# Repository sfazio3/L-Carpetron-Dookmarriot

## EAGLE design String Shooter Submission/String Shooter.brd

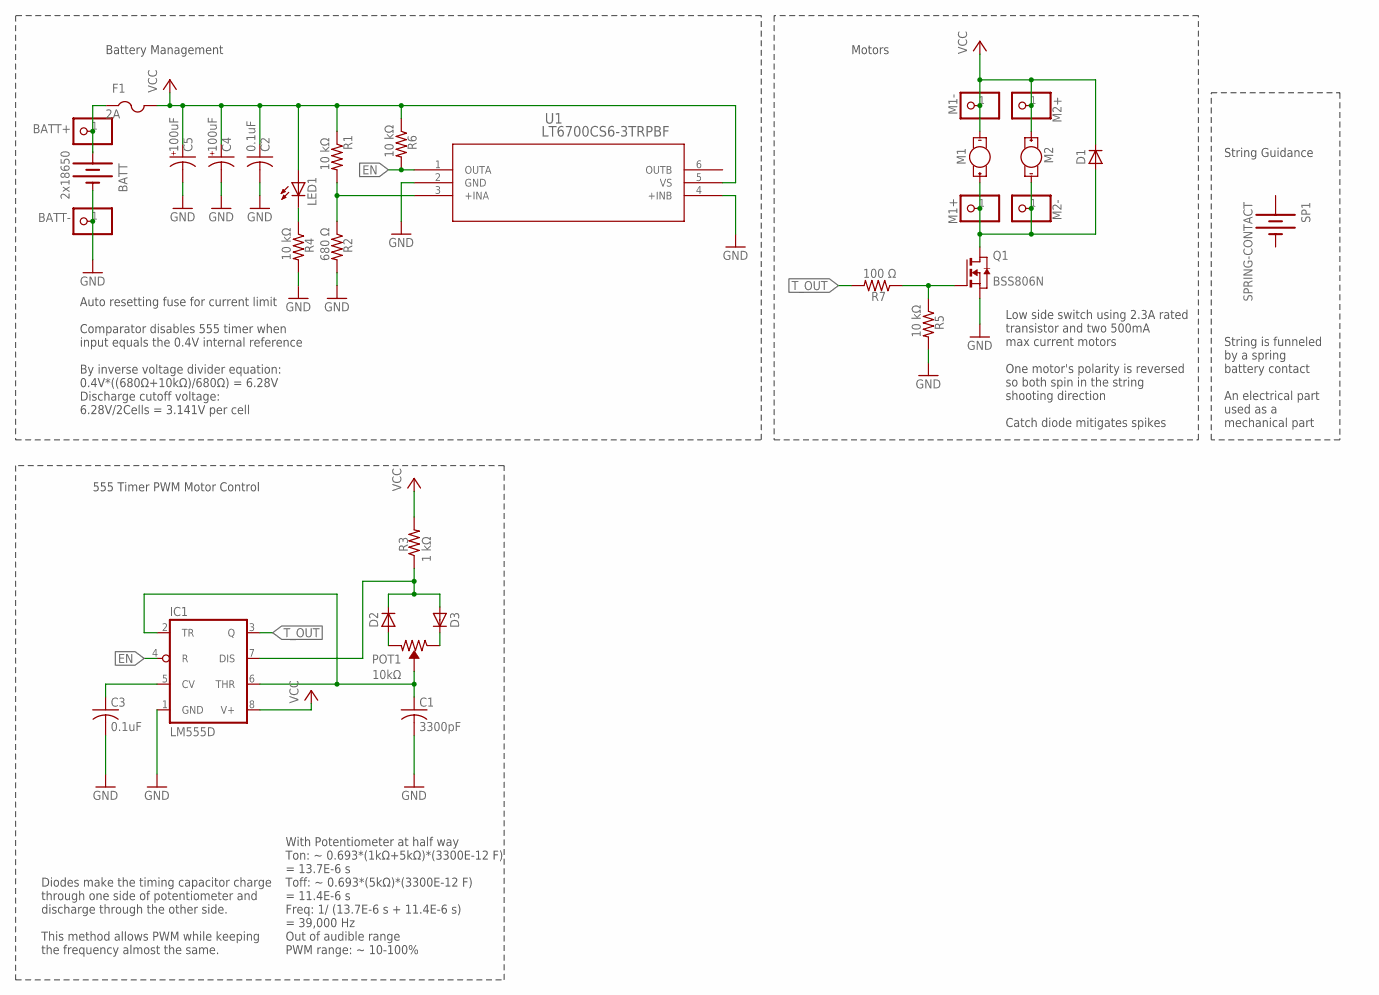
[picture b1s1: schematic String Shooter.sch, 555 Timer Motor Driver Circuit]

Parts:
BATT: 2x18650; BATTERY-CASE
BATT+: PINHD-1X1CB; 1X01-CLEANBIG
BATT-: PINHD-1X1CB; 1X01-CLEANBIG
C1: 3300pF; C0603
C2, C3: 0.1uF; C0603
C4, C5: 100uF; E22-6
D1, D2, D3: DIODE-DO-214AC; DO-214AC
F1: 2A; R1206
IC1: LM555D; SO08
LED1: LEDCHIP-LED0603; CHIP-LED0603
M1, M2: LITTLE-MOTOR; DC_MOTOR
M1+, M1-, M2+, M2-: PINHD-1X1CB; 1X01-CLEANBIG
POT1: 10kΩ; THUMBWHEEL-POT
Q1: BSS806N; SOT-23-3
R1, R4, R5, R6: 10 kΩ; R0603
R2: 680 Ω; R0603
R3: 1 kΩ; R0603
R7: 100 Ω; R0603
SP1: SPRING-CONTACT
U1: LT6700CS6-3TRPBF; TSOT-23_S6

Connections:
EN: IC1.4 (R), R6.2, U1.1 (OUTA)
GND: BATT-.1, C1.2, C2.2, C3.2, C4.-, C5.-, IC1.1 (GND), Q1.2 (S), R2.2, R4.2, R5.2, U1.2 (GND), U1.4 (+INB)
unnamed: D2.A, POT1.P$1 (CCW)
unnamed: D1.A, M1+.1, M2-.1, Q1.3 (D)
unnamed: C3.1, IC1.5 (CV)
unnamed: D3.C, POT1.P$3 (CW)
unnamed: D2.C, D3.A, IC1.7 (DIS), R3.1
unnamed: Q1.1 (G), R5.1, R7.1
unnamed: R1.2, R2.1, U1.3 (+INA)
unnamed: LED1.C, R4.1
unnamed: BATT+.1, F1.1
THR: C1.1, IC1.2 (TR), IC1.6 (THR), POT1.P$2 (WIPER)
T_OUT: IC1.3 (Q), R7.2
VCC: C2.1, C4.+, C5.+, D1.C, F1.2, IC1.8 (V+), LED1.A, M1-.1, M2+.1, R1.1, R3.2, R6.1, U1.5 (VS)

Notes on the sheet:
Diodes make the timing capacitor charge through one side of potentiometer and discharge through the other side. This method allows PWM while keeping the frequency almost the same.
Low side switch using 2.3A rated transistor and two 500mA max current motors One motor's polarity is reversed so both spin in the string shooting direction Catch diode mitigates spikes
555 Timer PWM Motor Control
Motors
Auto resetting fuse for current limit Comparator disables 555 timer when input equals the 0.4V internal reference By inverse voltage divider equation: 0.4V*((680Ω+10kΩ)/680Ω) = 6.28V Discharge cutoff voltage: 6.28V/2Cells = 3.141V per cell
Battery Management
String Guidance
String is funneled by a spring battery contact An electrical part used as a mechanical part
With Potentiometer at half way Ton: ~ 0.693*(1kΩ+5kΩ)*(3300E-12 F) = 13.7E-6 s Toff: ~ 0.693*(5kΩ)*(3300E-12 F) = 11.4E-6 s Freq: 1/ (13.7E-6 s + 11.4E-6 s) = 39,000 Hz Out of audible range PWM range: ~ 10-100%

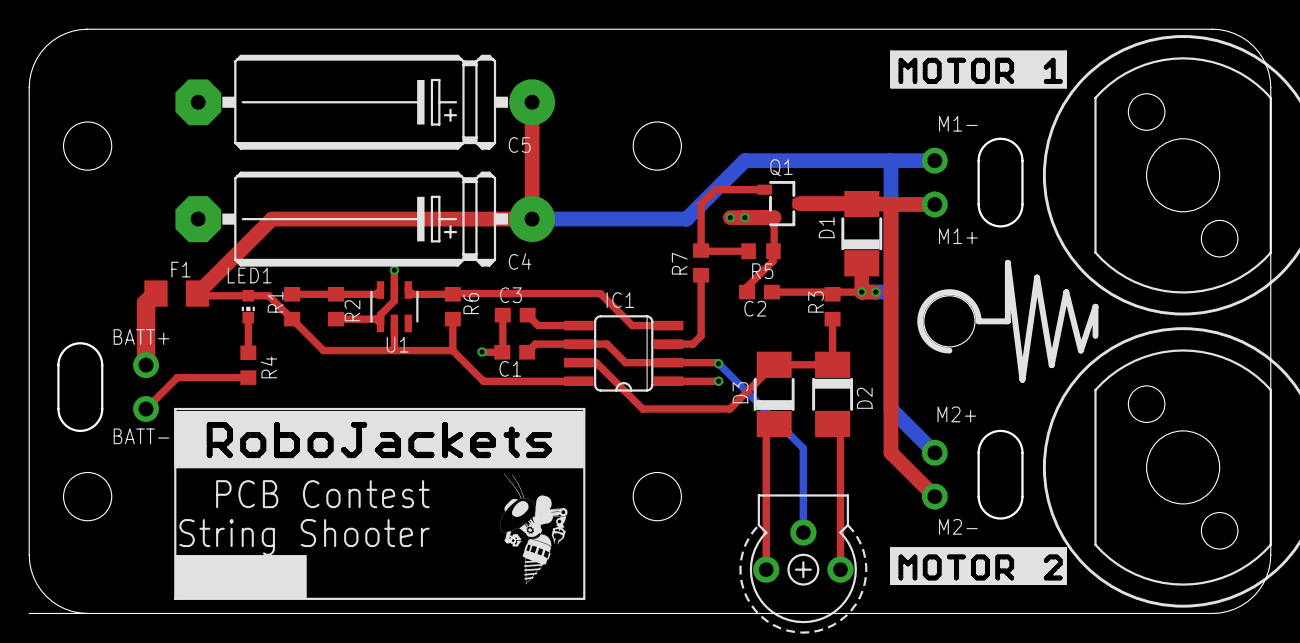
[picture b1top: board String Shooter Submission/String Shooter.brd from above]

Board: 2 copper layers, 85.0 x 40.0 mm, 35 parts (1 on the bottom side), 14 nets.

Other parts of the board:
U$1: MOTOR-1
U$2: MOTOR-2
U$3: ROBOBUZZ_0.4X
U$4: ROBOJACKETS

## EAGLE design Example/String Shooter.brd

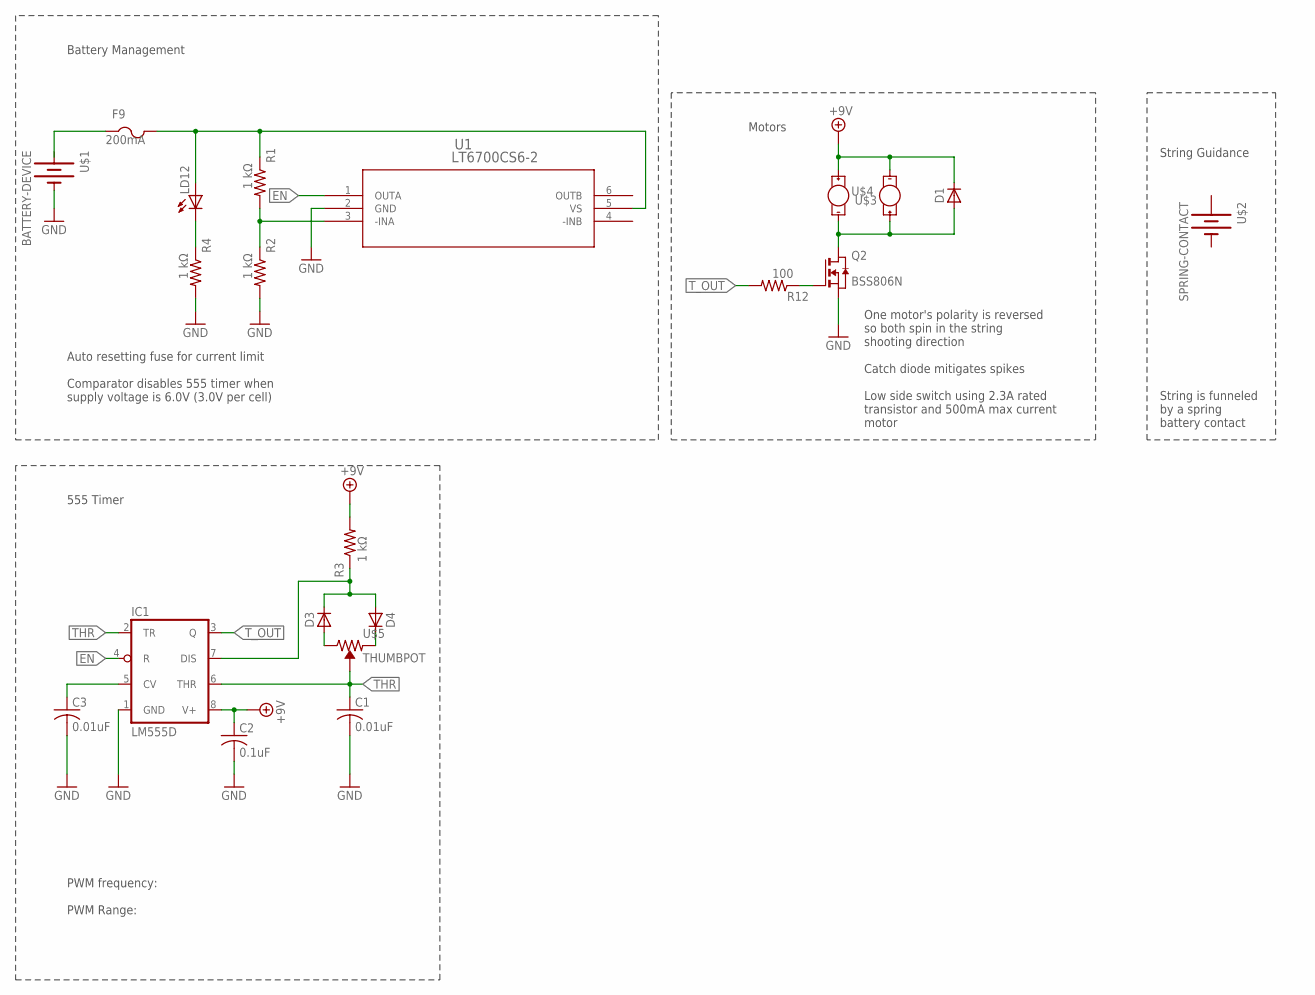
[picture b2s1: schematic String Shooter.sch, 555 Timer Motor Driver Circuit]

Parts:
C1, C3: 0.01uF; C0603
C2: 0.1uF; C0603
D1, D3, D4: DIODE-DO-214AC; DO-214AC
F9: 200mA; R1206
IC1: LM555D; SO08
LD12: BLUE; CHIP-LED0603
Q2: BSS806N; SOT-23-3
R1, R2, R3, R4: 1 kΩ; R0603
R12: 100; R0603
U1: LT6700CS6-2; TSOT-23_S6
U$1: BATTERY-DEVICE; BATTERY-CASE
U$2: SPRING-CONTACT
U$3, U$4: LITTLE-MOTOR; DC_MOTOR
U$5: THUMBPOT; THUMBWHEEL-POT

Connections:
+9V: C2.1, D1.C, IC1.8 (V+), R3.2
EN: IC1.4 (R), U1.1 (OUTA)
GND: C1.2, C2.2, C3.2, IC1.1 (GND), Q2.2 (S), R2.2, R4.2, U1.2 (GND)
unnamed: D4.C, U$5.P$1 (CCW)
unnamed: D1.A, Q2.3 (D)
unnamed: C3.1, IC1.5 (CV)
unnamed: D3.A, U$5.P$3 (CW)
unnamed: D3.C, D4.A, IC1.7 (DIS), R3.1
unnamed: Q2.1 (G), R12.1
unnamed: R1.2, R2.1, U1.3 (-INA)
unnamed: LD12.C, R4.1
unnamed: F9.2, LD12.A, R1.1, U1.5 (VS)
THR: C1.1, IC1.2 (TR), IC1.6 (THR), U$5.P$2 (WIPER)
T_OUT: IC1.3 (Q), R12.2

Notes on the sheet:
PWM frequency: PWM Range:
One motor's polarity is reversed so both spin in the string shooting direction Catch diode mitigates spikes Low side switch using 2.3A rated transistor and 500mA max current motor
555 Timer
Motors
Auto resetting fuse for current limit Comparator disables 555 timer when supply voltage is 6.0V (3.0V per cell)
Battery Management
String Guidance
String is funneled by a spring battery contact

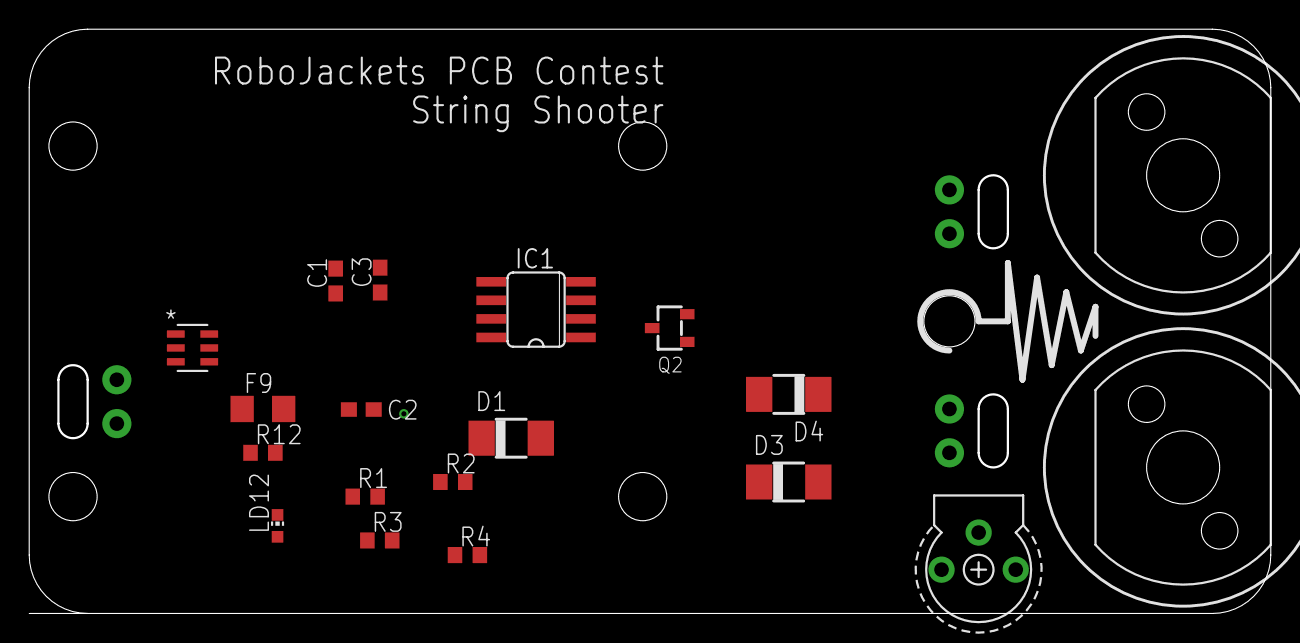
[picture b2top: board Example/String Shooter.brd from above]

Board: 2 copper layers, 85.0 x 40.0 mm, 21 parts (1 on the bottom side), 14 nets.

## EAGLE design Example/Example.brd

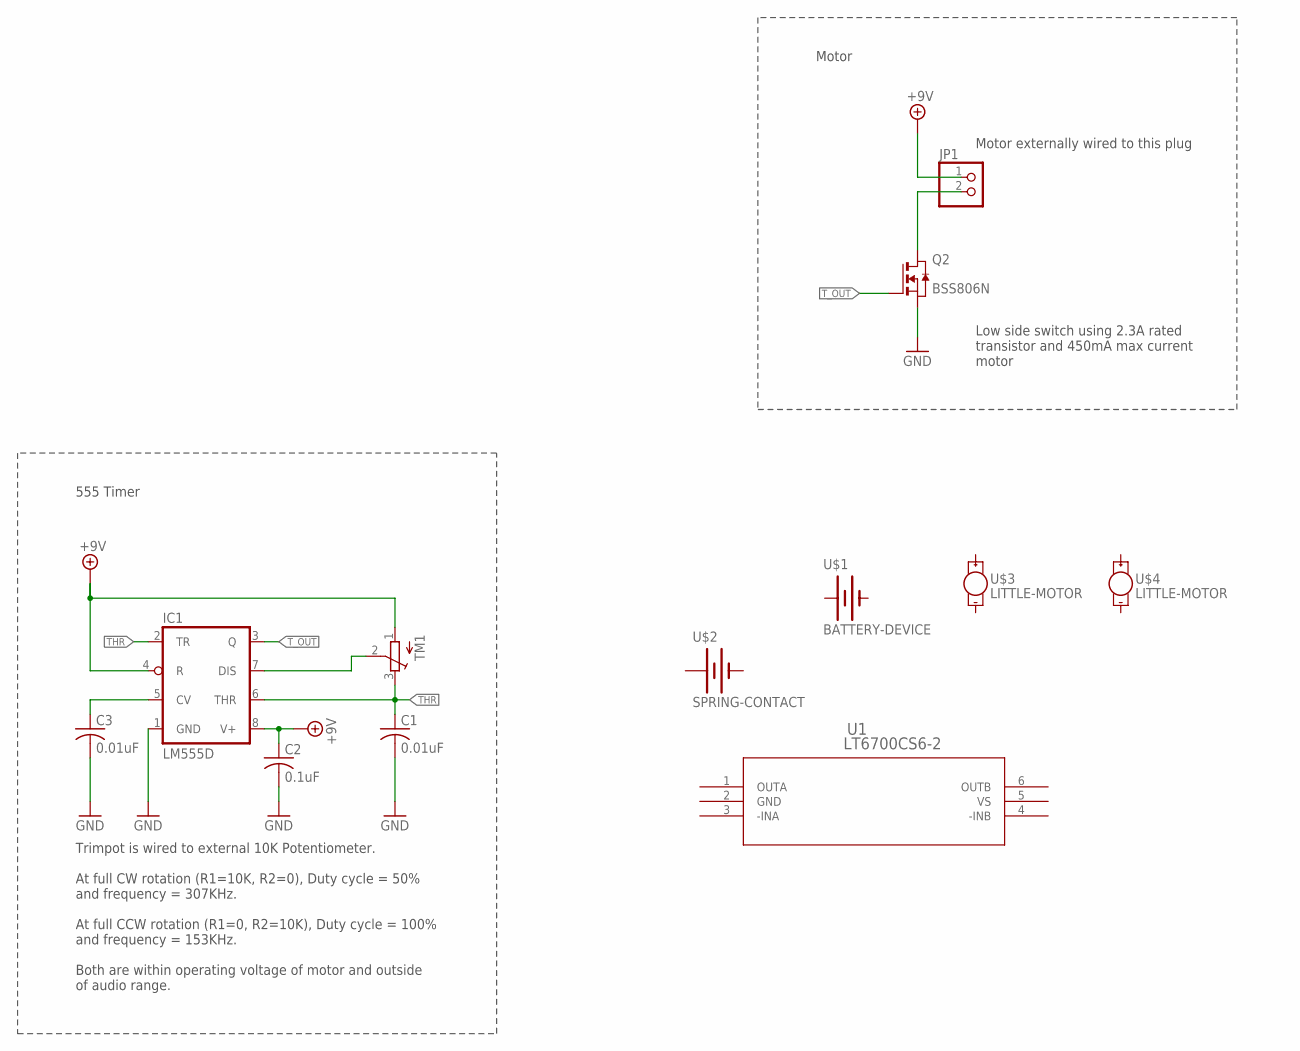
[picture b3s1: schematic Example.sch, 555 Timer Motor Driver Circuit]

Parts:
C1, C3: 0.01uF; C0603
C2: 0.1uF; C0603
IC1: LM555D; SO08
JP1: PINHD-1X2; 1X02
Q2: BSS806N; SOT-23-3
TM1: TRIMPOT3386; TRIM-3386
U1: LT6700CS6-2; TSOT-23_S6
U$1: BATTERY-DEVICE; BATTERY-CASE
U$2: SPRING-CONTACT
U$3, U$4: LITTLE-MOTOR; DC_MOTOR

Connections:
+9V: C2.1, IC1.4 (R), IC1.8 (V+), JP1.1, TM1.1 (A)
GND: C1.2, C2.2, C3.2, IC1.1 (GND), Q2.2 (S), U1.2 (GND)
unnamed: IC1.7 (DIS), TM1.2 (S)
unnamed: JP1.2, Q2.3 (D)
unnamed: C3.1, IC1.5 (CV)
THR: C1.1, IC1.2 (TR), IC1.6 (THR), TM1.3 (E)
T_OUT: IC1.3 (Q), Q2.1 (G)
VS: U1.5 (VS)

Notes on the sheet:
Trimpot is wired to external 10K Potentiometer. At full CW rotation (R1=10K, R2=0), Duty cycle = 50% and frequency = 307KHz. At full CCW rotation (R1=0, R2=10K), Duty cycle = 100% and frequency = 153KHz. Both are within operating voltage of motor and outside of audio range.
Motor externally wired to this plug
Low side switch using 2.3A rated transistor and 450mA max current motor
555 Timer
Motor

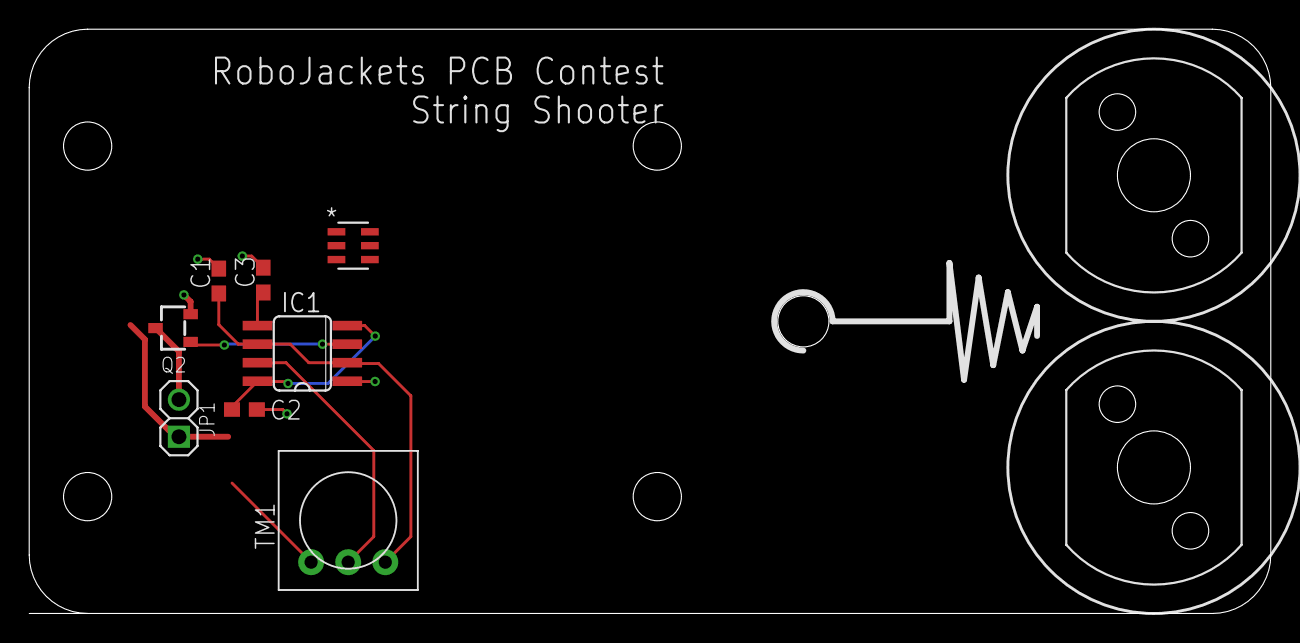
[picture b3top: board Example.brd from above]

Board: 2 copper layers, 85.0 x 40.0 mm, 12 parts (1 on the bottom side), 7 nets.

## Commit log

2021-01-09 Made footprints for motors, battery case, and guiding spring
2021-01-11 Made different string shooter schematic w/ components connected
2021-01-14 Routed board, schematic changes, prototype, and renders
2021-01-14 Charged Batteries and Installed much longer string
2021-01-14 Took out other demos and autosaves
